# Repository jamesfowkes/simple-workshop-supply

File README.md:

# simple-workshop-supply
A small PCB for a linear power supply

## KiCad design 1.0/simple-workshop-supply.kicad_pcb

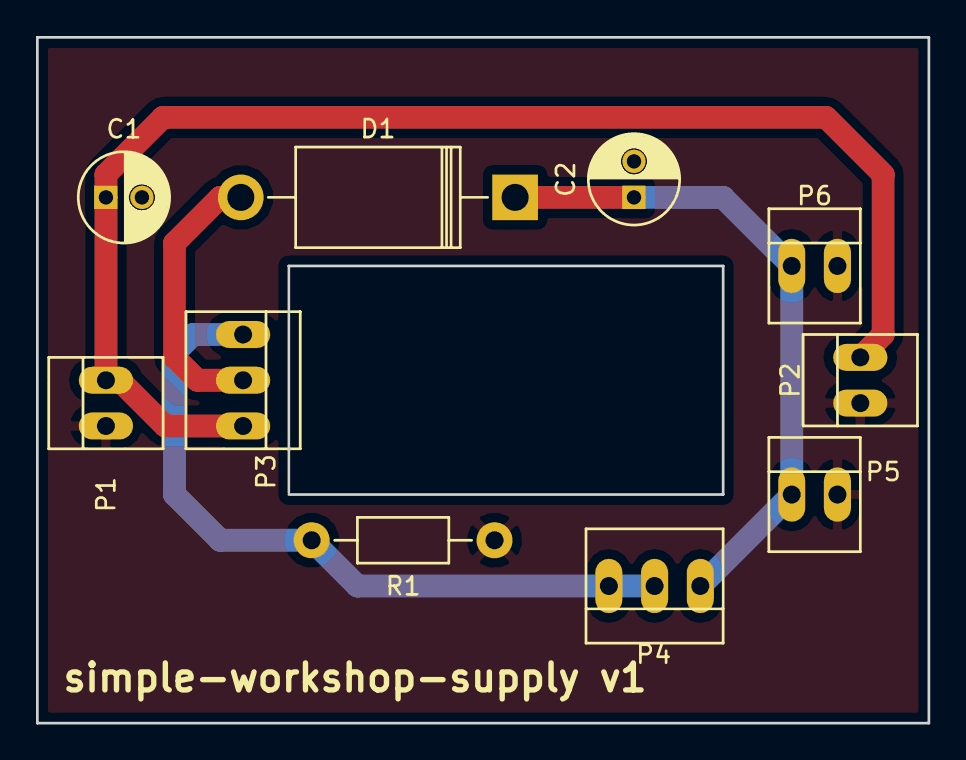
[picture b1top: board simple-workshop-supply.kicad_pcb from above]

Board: 2 copper layers, 49.5 x 38.1 mm, 10 parts (0 on the bottom side), 5 nets.

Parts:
C1, C2: CP; C_Radial_D5_L11_P2
D1: D_Schottky; Diode_DO-201AD_Horizontal_RM15
P1: IN; PINHEAD1-2
P2: OUT; PINHEAD1-2
P3: REG; PINHEAD1-3
P4: VR; PINHEAD1-3
P5: DISP; PINHEAD1-2
P6: VAR; PINHEAD1-2
R1: R; Resistor_Horizontal_RM10mm

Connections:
GND: C1.2, C2.2, P1.1, P2.1, P5.2, P6.2, R1.2
unnamed: C1.1, P1.2, P2.2, P3.3
unnamed: C2.1, D1.1, P4.1, P5.1, P6.1
unnamed: D1.2, P3.2
unnamed: P3.1, P4.2, P4.3, R1.1

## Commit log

2015-10-06 Version 1.0
